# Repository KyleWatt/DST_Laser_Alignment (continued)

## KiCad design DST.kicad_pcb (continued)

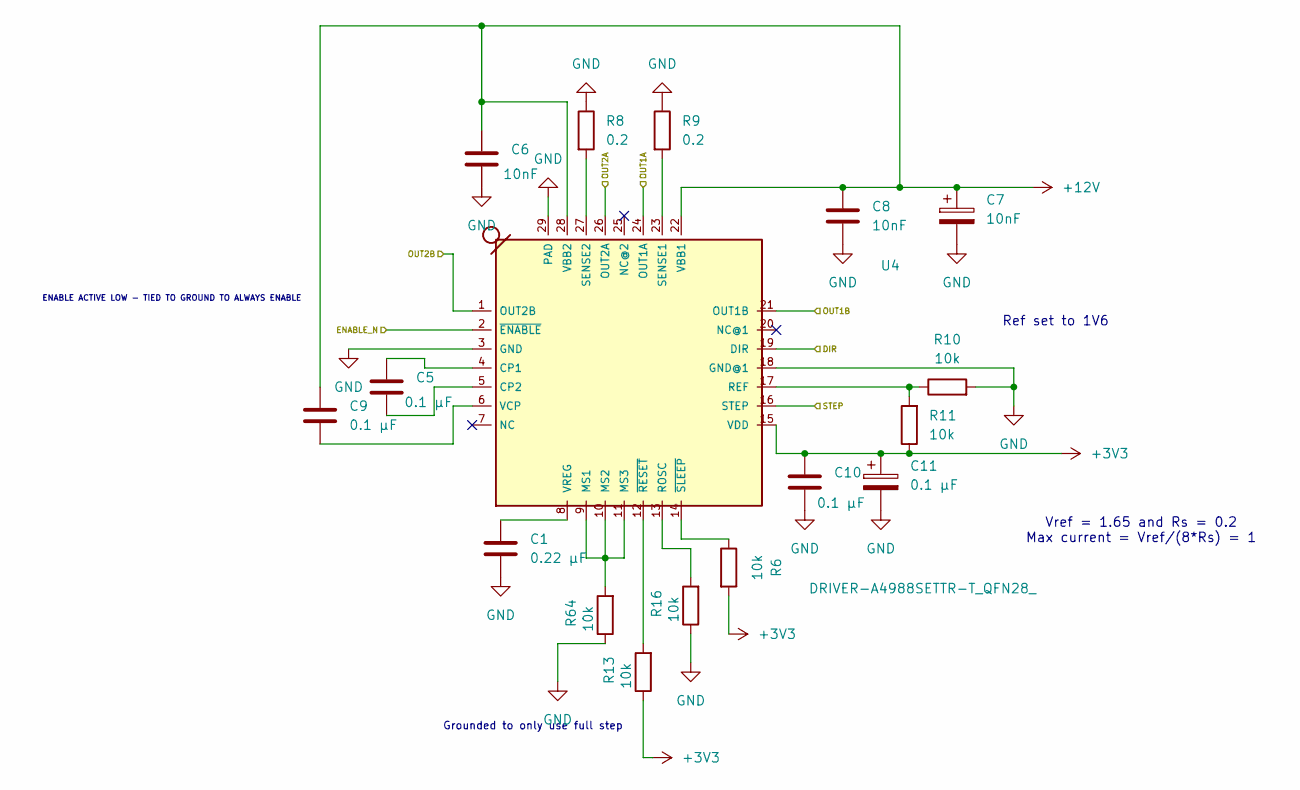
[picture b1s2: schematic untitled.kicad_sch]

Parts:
C1: 0.22 µF; C_0603_1608Metric
C5, C9, C10, C11: 0.1 µF; C_0603_1608Metric
C6, C7, C8: 10nF; C_0603_1608Metric
R6, R10, R11, R13, R16, R64: 10k; R_0805_2012Metric
R8, R9: 0.2; R_0805_2012Metric
U4: DRIVER-A4988SETTR-T_QFN28_; QFN28G_0.5-5X5MM; MPN A4988SETTR-T

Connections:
+3V3: C10.1, C11.1, R6.2, R11.1, R13.1, U4.15 (VDD); also elsewhere on the board
/DIR1: U4.19 (DIR); also elsewhere on the board
/ENABLE_N: U4.2 (~ENABLE); also elsewhere on the board
/OUT1A1: U4.24 (OUT1A); also elsewhere on the board
/OUT1B1: U4.21 (OUT1B); also elsewhere on the board
/OUT2A1: U4.26 (OUT2A); also elsewhere on the board
/OUT2B1: U4.1 (OUT2B); also elsewhere on the board
/STEP1: U4.16 (STEP); also elsewhere on the board
GND: C1.2, C6.2, C7.2, C8.2, C10.2, C11.2, R8.1, R9.1, R10.2, R16.1, R64.1, U4.3 (GND), U4.18 (GND@1), U4.29 (PAD); also elsewhere on the board
unnamed: C5.2, U4.4 (CP1)
unnamed: C5.1, U4.5 (CP2)
unnamed: R64.2, U4.9 (MS1), U4.10 (MS2), U4.11 (MS3)
unnamed: R10.1, R11.2, U4.17 (REF)
unnamed: R16.2, U4.13 (ROSC)
unnamed: R9.2, U4.23 (SENSE1)
unnamed: R8.2, U4.27 (SENSE2)
unnamed: C9.1, U4.6 (VCP)
unnamed: C1.1, U4.8 (VREG)
unnamed: R13.2, U4.12 (~RESET)
unnamed: R6.1, U4.14 (~SLEEP)

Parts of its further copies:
C12, C13, C16, C18, C20, C21, C24, C26, C28, C29, C32, C34, C36, C37, C40, C42, C44, C45, C48, C50, C52, C53, C56, C58, C60, C61, C64, C66, C68, C69, C72, C74, C76, C77, C80, C82, C84, C85, C88, C90, C92, C93, C96, C98: 0.1 µF; C_0603_1608Metric
C14, C17, C19, C22, C25, C27, C30, C33, C35, C38, C41, C43, C46, C49, C51, C54, C57, C59, C62, C65, C67, C70, C73, C75, C78, C81, C83, C86, C89, C91, C94, C97, C99: 10nF; C_0603_1608Metric
C15, C23, C31, C39, C47, C55, C63, C71, C79, C87, C95: 0.22 µF; C_0603_1608Metric
R14, R18, R19, R20, R21, R22, R24, R26, R27, R28, R29, R30, R32, R34, R35, R36, R37, R38, R40, R42, R43, R44, R45, R46, R48, R50, R51, R52, R53, R54, R56, R58, R59, R60, R61, R62, R66, R71, R72, R78, R81, R84, R86, R87, R88, R89, R90, R92, R94, R95, R96, R97, R98, R100, R102, R103, R104, R105, R106, R108, R110, R111, R112, R113, R114, R115: 10k; R_0805_2012Metric
R15, R17, R23, R25, R31, R33, R39, R41, R47, R49, R55, R57, R63, R65, R83, R85, R91, R93, R99, R101, R107, R109: 0.2; R_0805_2012Metric
U5, U6, U7, U8, U9, U10, U11, U12, U13, U14, U15: DRIVER-A4988SETTR-T_QFN28_; QFN28G_0.5-5X5MM; MPN A4988SETTR-T

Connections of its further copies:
+3V3: C16.1, C18.1, C24.1, C26.1, C32.1, C34.1, C40.1, C42.1, C48.1, C50.1, C56.1, C58.1, C64.1, C66.1, C72.1, C74.1, C80.1, C82.1, C88.1, C90.1, C96.1, C98.1, R14.1, R19.2, R20.1, R22.1, R27.2, R28.1, R30.1, R35.2, R36.1, R38.1, R43.2, R44.1, R46.1, R51.2, R52.1, R54.1, R59.2, R60.1, R62.1, R71.2, R72.1, R81.1, R87.2, R88.1, R90.1, R95.2, R96.1, R98.1, R103.2, R104.1, R106.1, R111.2, R112.1, U5.15 (VDD), U6.15 (VDD), U7.15 (VDD), U8.15 (VDD), U9.15 (VDD), U10.15 (VDD), U11.15 (VDD), U12.15 (VDD), U13.15 (VDD), U14.15 (VDD), U15.15 (VDD); also elsewhere on the board
/DIR2: U5.19 (DIR); also elsewhere on the board
/DIR3: U6.19 (DIR); also elsewhere on the board
/DIR4: U7.19 (DIR); also elsewhere on the board
/DIR5: U8.19 (DIR); also elsewhere on the board
/DIR6: U9.19 (DIR); also elsewhere on the board
/DIR7: U10.19 (DIR); also elsewhere on the board
/DIR8: U11.19 (DIR); also elsewhere on the board
/DIR9: U12.19 (DIR); also elsewhere on the board
/DIR10: U13.19 (DIR); also elsewhere on the board
/DIR11: U14.19 (DIR); also elsewhere on the board
/DIR12: U15.19 (DIR); also elsewhere on the board
/ENABLE_N: U5.2 (~ENABLE), U6.2 (~ENABLE), U7.2 (~ENABLE), U8.2 (~ENABLE), U9.2 (~ENABLE), U10.2 (~ENABLE), U11.2 (~ENABLE), U12.2 (~ENABLE), U13.2 (~ENABLE), U14.2 (~ENABLE), U15.2 (~ENABLE); also elsewhere on the board
/OUT1A2: U5.24 (OUT1A); also elsewhere on the board
/OUT1A3: U6.24 (OUT1A); also elsewhere on the board
/OUT1A4: U7.24 (OUT1A); also elsewhere on the board
/OUT1A5: U8.24 (OUT1A); also elsewhere on the board
/OUT1A6: U9.24 (OUT1A); also elsewhere on the board
/OUT1A7: U10.24 (OUT1A); also elsewhere on the board
/OUT1A8: U11.24 (OUT1A); also elsewhere on the board
/OUT1A9: U12.24 (OUT1A); also elsewhere on the board
/OUT1A10: U13.24 (OUT1A); also elsewhere on the board
/OUT1A11: U14.24 (OUT1A); also elsewhere on the board
/OUT1A12: U15.24 (OUT1A); also elsewhere on the board
/OUT1B2: U5.21 (OUT1B); also elsewhere on the board
/OUT1B3: U6.21 (OUT1B); also elsewhere on the board
/OUT1B4: U7.21 (OUT1B); also elsewhere on the board
/OUT1B5: U8.21 (OUT1B); also elsewhere on the board
/OUT1B6: U9.21 (OUT1B); also elsewhere on the board
/OUT1B7: U10.21 (OUT1B); also elsewhere on the board
/OUT1B8: U11.21 (OUT1B); also elsewhere on the board
/OUT1B9: U12.21 (OUT1B); also elsewhere on the board
/OUT1B10: U13.21 (OUT1B); also elsewhere on the board
/OUT1B11: U14.21 (OUT1B); also elsewhere on the board
/OUT1B12: U15.21 (OUT1B); also elsewhere on the board
/OUT2A2: U5.26 (OUT2A); also elsewhere on the board
/OUT2A3: U6.26 (OUT2A); also elsewhere on the board
/OUT2A4: U7.26 (OUT2A); also elsewhere on the board
/OUT2A5: U8.26 (OUT2A); also elsewhere on the board
/OUT2A6: U9.26 (OUT2A); also elsewhere on the board
/OUT2A7: U10.26 (OUT2A); also elsewhere on the board
/OUT2A8: U11.26 (OUT2A); also elsewhere on the board
/OUT2A9: U12.26 (OUT2A); also elsewhere on the board
/OUT2A10: U13.26 (OUT2A); also elsewhere on the board
/OUT2A11: U14.26 (OUT2A); also elsewhere on the board
/OUT2A12: U15.26 (OUT2A); also elsewhere on the board
/OUT2B2: U5.1 (OUT2B); also elsewhere on the board
/OUT2B3: U6.1 (OUT2B); also elsewhere on the board
/OUT2B4: U7.1 (OUT2B); also elsewhere on the board
/OUT2B5: U8.1 (OUT2B); also elsewhere on the board
/OUT2B6: U9.1 (OUT2B); also elsewhere on the board
/OUT2B7: U10.1 (OUT2B); also elsewhere on the board
/OUT2B8: U11.1 (OUT2B); also elsewhere on the board
/OUT2B9: U12.1 (OUT2B); also elsewhere on the board
/OUT2B10: U13.1 (OUT2B); also elsewhere on the board
/OUT2B11: U14.1 (OUT2B); also elsewhere on the board
/OUT2B12: U15.1 (OUT2B); also elsewhere on the board
/STEP2: U5.16 (STEP); also elsewhere on the board
/STEP3: U6.16 (STEP); also elsewhere on the board
/STEP4: U7.16 (STEP); also elsewhere on the board
/STEP5: U8.16 (STEP); also elsewhere on the board
/STEP6: U9.16 (STEP); also elsewhere on the board
/STEP7: U10.16 (STEP); also elsewhere on the board
/STEP8: U11.16 (STEP); also elsewhere on the board
/STEP9: U12.16 (STEP); also elsewhere on the board
/STEP10: U13.16 (STEP); also elsewhere on the board
/STEP11: U14.16 (STEP); also elsewhere on the board
/STEP12: U15.16 (STEP); also elsewhere on the board
GND: C14.2, C15.2, C16.2, C17.2, C18.2, C19.2, C22.2, C23.2, C24.2, C25.2, C26.2, C27.2, C30.2, C31.2, C32.2, C33.2, C34.2, C35.2, C38.2, C39.2, C40.2, C41.2, C42.2, C43.2, C46.2, C47.2, C48.2, C49.2, C50.2, C51.2, C54.2, C55.2, C56.2, C57.2, C58.2, C59.2, C62.2, C63.2, C64.2, C65.2, C66.2, C67.2, C70.2, C71.2, C72.2, C73.2, C74.2, C75.2, C78.2, C79.2, C80.2, C81.2, C82.2, C83.2, C86.2, C87.2, C88.2, C89.2, C90.2, C91.2, C94.2, C95.2, C96.2, C97.2, C98.2, C99.2, R15.1, R17.1, R18.1, R21.2, R23.1, R24.1, R25.1, R26.1, R29.2, R31.1, R32.1, R33.1, R34.1, R37.2, R39.1, R40.1, R41.1, R42.1, R45.2, R47.1, R48.1, R49.1, R50.1, R53.2, R55.1, R56.1, R57.1, R58.1, R61.2, R63.1, R65.1, R66.1, R78.2, R83.1, R84.1, R85.1, R86.1, R89.2, R91.1, R92.1, R93.1, R94.1, R97.2, R99.1, R100.1, R101.1, R102.1, R105.2, R107.1, R108.1, R109.1, R110.1, R113.2, R114.1, R115.1, U5.3 (GND), U5.18 (GND@1), U5.29 (PAD), U6.3 (GND), U6.18 (GND@1), U6.29 (PAD), U7.3 (GND), U7.18 (GND@1), U7.29 (PAD), U8.3 (GND), U8.18 (GND@1), U8.29 (PAD), U9.3 (GND), U9.18 (GND@1), U9.29 (PAD), U10.3 (GND), U10.18 (GND@1), U10.29 (PAD), U11.3 (GND), U11.18 (GND@1), U11.29 (PAD), U12.3 (GND), U12.18 (GND@1), U12.29 (PAD), U13.3 (GND), U13.18 (GND@1), U13.29 (PAD), U14.3 (GND), U14.18 (GND@1), U14.29 (PAD), U15.3 (GND), U15.18 (GND@1), U15.29 (PAD); also elsewhere on the board
unnamed: C13.2, U5.4 (CP1)
unnamed: C13.1, U5.5 (CP2)
unnamed: R66.2, U5.9 (MS1), U5.10 (MS2), U5.11 (MS3)
unnamed: R20.2, R21.1, U5.17 (REF)
unnamed: R18.2, U5.13 (ROSC)
unnamed: R17.2, U5.23 (SENSE1)
unnamed: R15.2, U5.27 (SENSE2)
unnamed: C12.1, U5.6 (VCP)
unnamed: C15.1, U5.8 (VREG)
unnamed: R14.2, U5.12 (~RESET)
unnamed: R19.1, U5.14 (~SLEEP)
unnamed: C21.2, U6.4 (CP1)
unnamed: C21.1, U6.5 (CP2)
unnamed: R84.2, U6.9 (MS1), U6.10 (MS2), U6.11 (MS3)
unnamed: R28.2, R29.1, U6.17 (REF)
unnamed: R24.2, U6.13 (ROSC)
unnamed: R25.2, U6.23 (SENSE1)
unnamed: R23.2, U6.27 (SENSE2)
unnamed: C20.1, U6.6 (VCP)
unnamed: C23.1, U6.8 (VREG)
unnamed: R22.2, U6.12 (~RESET)
unnamed: R27.1, U6.14 (~SLEEP)
unnamed: C29.2, U7.4 (CP1)
unnamed: C29.1, U7.5 (CP2)
unnamed: R86.2, U7.9 (MS1), U7.10 (MS2), U7.11 (MS3)
unnamed: R36.2, R37.1, U7.17 (REF)
unnamed: R26.2, U7.13 (ROSC)
unnamed: R33.2, U7.23 (SENSE1)
unnamed: R31.2, U7.27 (SENSE2)
unnamed: C28.1, U7.6 (VCP)
unnamed: C31.1, U7.8 (VREG)
unnamed: R30.2, U7.12 (~RESET)
unnamed: R35.1, U7.14 (~SLEEP)
unnamed: C37.2, U8.4 (CP1)
unnamed: C37.1, U8.5 (CP2)
unnamed: R92.2, U8.9 (MS1), U8.10 (MS2), U8.11 (MS3)
unnamed: R44.2, R45.1, U8.17 (REF)
unnamed: R32.2, U8.13 (ROSC)
unnamed: R41.2, U8.23 (SENSE1)
unnamed: R39.2, U8.27 (SENSE2)
unnamed: C36.1, U8.6 (VCP)
unnamed: C39.1, U8.8 (VREG)
unnamed: R38.2, U8.12 (~RESET)
unnamed: R43.1, U8.14 (~SLEEP)
unnamed: C45.2, U9.4 (CP1)
unnamed: C45.1, U9.5 (CP2)
unnamed: R94.2, U9.9 (MS1), U9.10 (MS2), U9.11 (MS3)
unnamed: R52.2, R53.1, U9.17 (REF)
unnamed: R34.2, U9.13 (ROSC)
unnamed: R49.2, U9.23 (SENSE1)
unnamed: R47.2, U9.27 (SENSE2)
unnamed: C44.1, U9.6 (VCP)
unnamed: C47.1, U9.8 (VREG)
unnamed: R46.2, U9.12 (~RESET)
unnamed: R51.1, U9.14 (~SLEEP)
unnamed: C53.2, U10.4 (CP1)
unnamed: C53.1, U10.5 (CP2)
unnamed: R100.2, U10.9 (MS1), U10.10 (MS2), U10.11 (MS3)
unnamed: R60.2, R61.1, U10.17 (REF)
unnamed: R40.2, U10.13 (ROSC)
unnamed: R57.2, U10.23 (SENSE1)
unnamed: R55.2, U10.27 (SENSE2)
unnamed: C52.1, U10.6 (VCP)
unnamed: C55.1, U10.8 (VREG)
unnamed: R54.2, U10.12 (~RESET)
unnamed: R59.1, U10.14 (~SLEEP)
unnamed: C61.2, U11.4 (CP1)
unnamed: C61.1, U11.5 (CP2)
unnamed: R102.2, U11.9 (MS1), U11.10 (MS2), U11.11 (MS3)
unnamed: R72.2, R78.1, U11.17 (REF)
unnamed: R42.2, U11.13 (ROSC)
unnamed: R65.2, U11.23 (SENSE1)
unnamed: R63.2, U11.27 (SENSE2)
unnamed: C60.1, U11.6 (VCP)
unnamed: C63.1, U11.8 (VREG)
unnamed: R62.2, U11.12 (~RESET)
unnamed: R71.1, U11.14 (~SLEEP)
unnamed: C69.2, U12.4 (CP1)
unnamed: C69.1, U12.5 (CP2)
unnamed: R108.2, U12.9 (MS1), U12.10 (MS2), U12.11 (MS3)
unnamed: R88.2, R89.1, U12.17 (REF)
unnamed: R48.2, U12.13 (ROSC)
unnamed: R85.2, U12.23 (SENSE1)
unnamed: R83.2, U12.27 (SENSE2)
unnamed: C68.1, U12.6 (VCP)
unnamed: C71.1, U12.8 (VREG)
unnamed: R81.2, U12.12 (~RESET)
unnamed: R87.1, U12.14 (~SLEEP)
unnamed: C77.2, U13.4 (CP1)
unnamed: C77.1, U13.5 (CP2)
unnamed: R110.2, U13.9 (MS1), U13.10 (MS2), U13.11 (MS3)
unnamed: R96.2, R97.1, U13.17 (REF)
unnamed: R50.2, U13.13 (ROSC)
unnamed: R93.2, U13.23 (SENSE1)
unnamed: R91.2, U13.27 (SENSE2)
unnamed: C76.1, U13.6 (VCP)
unnamed: C79.1, U13.8 (VREG)
unnamed: R90.2, U13.12 (~RESET)
unnamed: R95.1, U13.14 (~SLEEP)
unnamed: C85.2, U14.4 (CP1)
unnamed: C85.1, U14.5 (CP2)
unnamed: R114.2, U14.9 (MS1), U14.10 (MS2), U14.11 (MS3)
unnamed: R104.2, R105.1, U14.17 (REF)
unnamed: R56.2, U14.13 (ROSC)
unnamed: R101.2, U14.23 (SENSE1)
unnamed: R99.2, U14.27 (SENSE2)
unnamed: C84.1, U14.6 (VCP)
unnamed: C87.1, U14.8 (VREG)
unnamed: R98.2, U14.12 (~RESET)
unnamed: R103.1, U14.14 (~SLEEP)
unnamed: C93.2, U15.4 (CP1)
unnamed: C93.1, U15.5 (CP2)
unnamed: R115.2, U15.9 (MS1), U15.10 (MS2), U15.11 (MS3)
unnamed: R112.2, R113.1, U15.17 (REF)
unnamed: R58.2, U15.13 (ROSC)
unnamed: R109.2, U15.23 (SENSE1)
unnamed: R107.2, U15.27 (SENSE2)
unnamed: C92.1, U15.6 (VCP)
unnamed: C95.1, U15.8 (VREG)
unnamed: R106.2, U15.12 (~RESET)
unnamed: R111.1, U15.14 (~SLEEP)

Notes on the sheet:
ENABLE ACTIVE LOW - TIED TO GROUND TO ALWAYS ENABLE
Ref set to 1V6
Vref = 1.65 and Rs = 0.2 Max current = Vref/(8*Rs) = 1
Grounded to only use full step

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
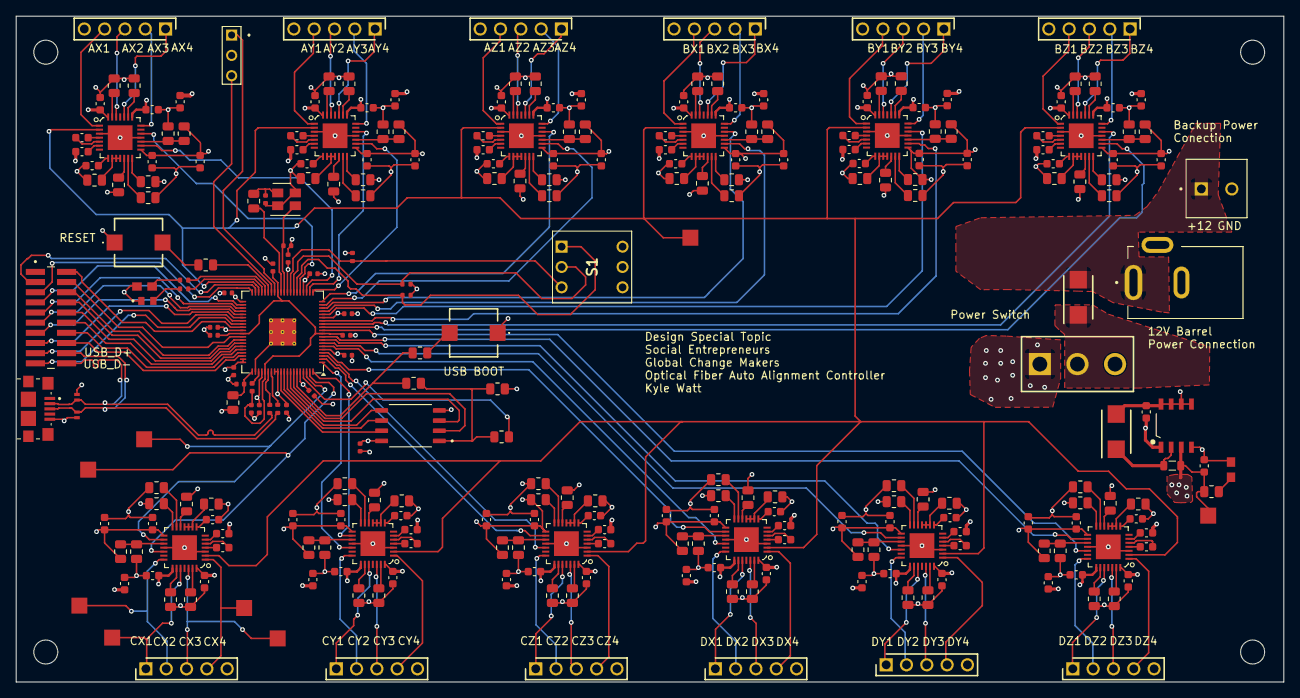
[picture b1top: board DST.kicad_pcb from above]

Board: 6 copper layers, 158.5 x 83.3 mm, 281 parts (0 on the bottom side), 259 nets.

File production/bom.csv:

Designator,Footprint,Quantity,Value,LCSC Part #
"C1, C15, C23, C31, C39, C47, C55, C63, C71, C79, C87, C95",0603,12,0.22 µF,
"C10, C11, C115, C116, C12, C13, C16, C18, C20, C21, C24, C26, C28, C29, C32, C34, C36, C37, C40, C42, C44, C45, C48, C5, C50, C52, C53, C56, C58, C60, C61, C64, C66, C68, C69, C72, C74, C76, C77, C80, C82, C84, C85, C88, C9, C90, C92, C93, C96, C98",0603,50,0.1 µF,
"C100, C101",0402,2,1u,
"C102, C103",0402,2,10n,
"C104, C105, C106, C107, C108, C109, C111, C3",0402,8,100n,
"C110, C112, C113, C114",0402,4,4.7u,
"C14, C17, C19, C22, C25, C27, C30, C33, C35, C38, C41, C43, C46, C49, C51, C54, C57, C59, C6, C62, C65, C67, C7, C70, C73, C75, C78, C8, C81, C83, C86, C89, C91, C94, C97, C99",0603,36,10nF,
"C2, C4",0402,2,15p,
"D1, D2",DIOM5436X244N,2,D_Schottky,
"D3, D4",PESD5V0S1BL315,2,PTVS3V3D1BALYL,
D6,LED_KT-0603R,1,KT-0603R,
J1,PHOENIX_1727010,1,1727010,
"J10, J11, J12, J15, J16, J17, J4, J5, J6, J7, J8, J9",HDRV5W62P0X254_1X5_1270X240X1624P,12,77311-462K05LF,
J13,XKB_DC-005-5A-2.0,1,DC-005-5A-2.0,
J14,TE_1981568-1,1,1981568-1,
J2,TE_5-146280-3,1,5-146280-3,
J3,AMPHENOL_20021121-00020C4LF,1,20021121-00020C4LF,
L1,0402,1,3.3u,
L2,0805,1,47uH,
"LED1, LED2",LEDM2012X80N,2,150080GS75000,
"R10, R100, R102, R103, R104, R105, R106, R108, R11, R110, R111, R112, R113, R114, R115, R13, R14, R16, R18, R19, R20, R21, R22, R24, R26, R27, R28, R29, R30, R32, R34, R35, R36, R37, R38, R40, R42, R43, R44, R45, R46, R48, R50, R51, R52, R53, R54, R56, R58, R59, R6, R60, R61, R62, R64, R66, R71, R72, R78, R81, R84, R86, R87, R88, R89, R90, R92, R94, R95, R96, R97, R98",0805,72,10k,
"R101, R107, R109, R15, R17, R23, R25, R31, R33, R39, R41, R47, R49, R55, R57, R63, R65, R8, R83, R85, R9, R91, R93, R99",0805,24,0.2,
R3,0805,1,0,
"R4, R5, R69",0805,3,1k,
"R67, R68",0402,2,27,
R70,0805,1,33,
"R73, R74, R75",0402,3,10k,
"R76, R77",0805,2,DNF,
R79,0805,1,60,
R80,0402,1,60,
R82,0402,1,100,
S1,NDS03V,1,NDS-03V,
S2,1MS3T1B1M2QES,1,1MS3T1B1M2QES,
"SW1, SW2",SPEH110101,2,SW_Push,
"TP1, TP10, TP11, TP12, TP2, TP3, TP8, TP9",TestPoint_Pad_2.0x2.0mm,8,TestPoint,
U1,QFN-80-1EP_10x10mm_P0.4mm_EP3.4x3.4mm_ThermalVias,1,RP2350B-QFN80,
"U10, U11, U12, U13, U14, U15, U4, U5, U6, U7, U8, U9",QFN28G_0.5-5X5MM,12,DRIVER-A4988SETTR-T_QFN28_,A4988SETTR-T
U16,SOIC8-1.27-5X4MM,1,PMIC-AP1509-SG-13_SOIC8_,AP1509-SG-13
U2,ABM8-272-T3,1,ABM8-272-T3,
U3,SOIC127P790X216-8N,1,W25Q128JVSIQ,

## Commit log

2025-03-15 Inital KiCad schematic for autolaser alignment circuit
2025-04-27 updated kicad files
2025-05-22 newsest changes
